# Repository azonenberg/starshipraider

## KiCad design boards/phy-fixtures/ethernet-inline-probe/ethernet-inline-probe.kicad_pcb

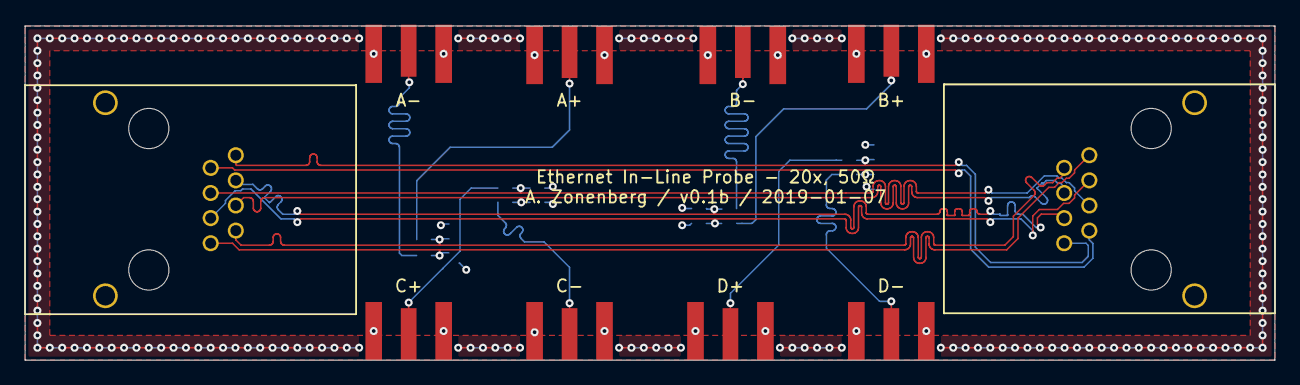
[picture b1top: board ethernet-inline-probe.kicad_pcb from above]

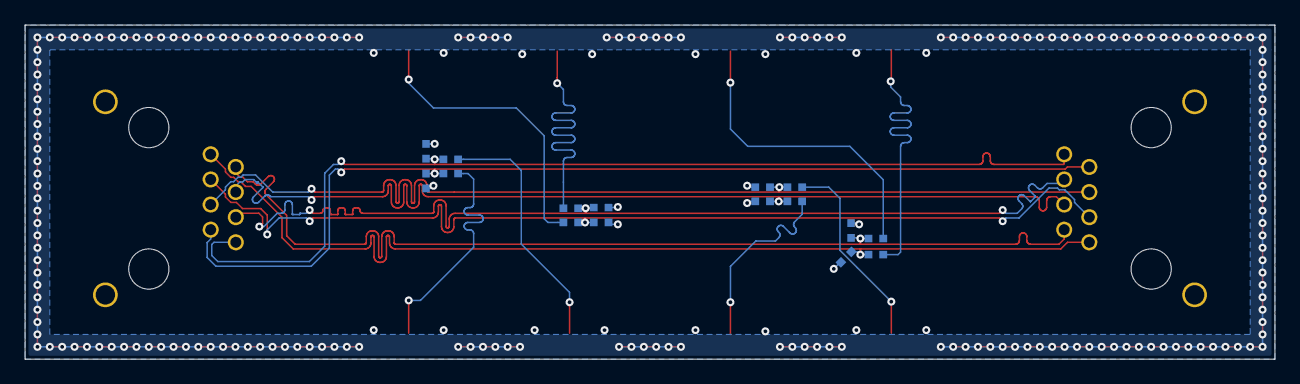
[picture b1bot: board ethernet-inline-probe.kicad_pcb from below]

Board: 4 copper layers, 101.0 x 27.0 mm, 26 parts (16 on the bottom side), 17 nets.

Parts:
J1, J6: STEWART_SS_60000_009; CONN_STEWART_SS60000_009
J2, J3, J4, J5, J7, J8, J9, J10: SMA-J-P-H-ST-EM1; CONN_SMA_EDGE_SAMTEC_SMA_J_P_H_ST_EM1
R1, R2, R3, R4, R5, R6, R7, R8: 953; EIA_0402_RES_NOSILK
R9, R10, R11, R12, R13, R14, R15, R16: 100K; EIA_0402_RES_NOSILK

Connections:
/CH1_N: J1.2, J6.2, R2.2, R10.2
/CH1_P: J1.1, J6.1, R1.2, R9.2
/CH2_N: J1.6, J6.6, R4.2, R12.2
/CH2_P: J1.3, J6.3, R3.2, R11.2
/CH3_N: J1.5, J6.5, R6.2, R14.2
/CH3_P: J1.4, J6.4, R5.2, R13.2
/CH4_N: J1.8, J6.8, R8.2, R16.2
/CH4_P: J1.7, J6.7, R7.2, R15.2
/GND: J1.9, J2.2, J3.2, J4.2, J5.2, J6.9, J7.2, J8.2, J9.2, J10.2, R9.1, R10.1, R11.1, R12.1, R13.1, R14.1, R15.1, R16.1
unnamed: J2.1, R1.1
unnamed: J3.1, R2.1
unnamed: J4.1, R3.1
unnamed: J5.1, R4.1
unnamed: J7.1, R5.1
unnamed: J8.1, R6.1
unnamed: J9.1, R7.1
unnamed: J10.1, R8.1

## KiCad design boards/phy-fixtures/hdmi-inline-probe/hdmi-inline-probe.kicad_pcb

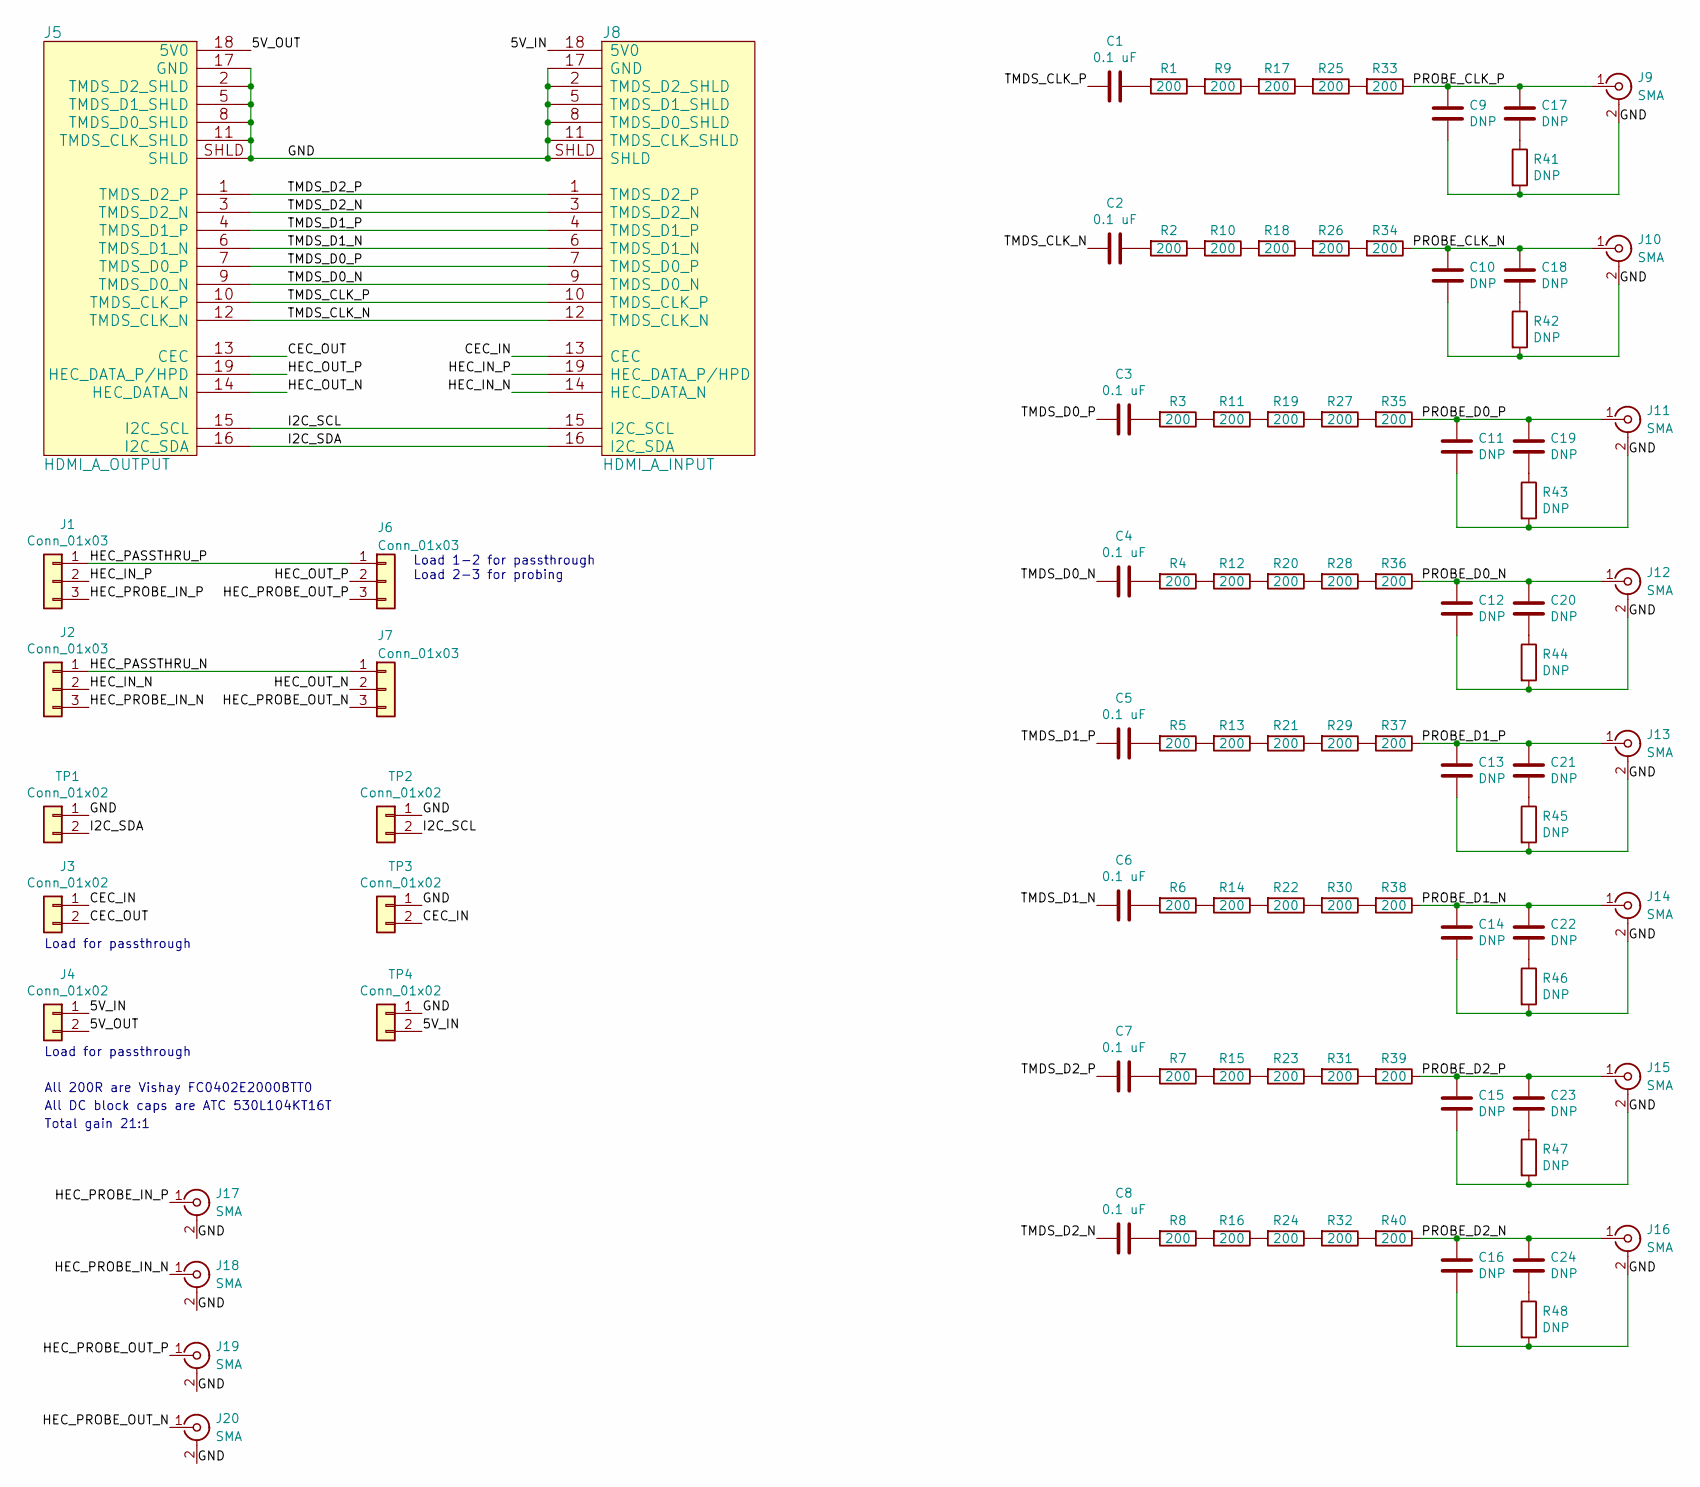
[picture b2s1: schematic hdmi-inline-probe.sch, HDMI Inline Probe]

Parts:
C1, C2, C3, C4, C5, C6, C7, C8: 0.1 uF; EIA_0402_CAP_NOSILK
C9, C10, C11, C12, C13, C14, C15, C16, C17, C18, C19, C20, C21, C22, C23, C24: DNP; EIA_0402_CAP_NOSILK
J1, J2, J6, J7: Conn_01x03; CONN_HEADER_2.54MM_1x3
J3, J4: Conn_01x02; CONN_HEADER_2.54MM_1x2
J5: HDMI_A_OUTPUT; CONN_HDMI_SAMTEC_HDMR_19_01_S_SM
J8: HDMI_A_INPUT; CONN_HDMI_SAMTEC_HDMR_19_01_S_SM
J9, J10, J11, J12, J13, J14, J15, J16, J17, J18, J19, J20: SMA; CONN_SMA_EDGE_SAMTEC_SMA_J_P_H_ST_EM1
R1, R2, R3, R4, R5, R6, R7, R8, R9, R10, R11, R12, R13, R14, R15, R16, R17, R18, R19, R20, R21, R22, R23, R24, R25, R26, R27, R28, R29, R30, R31, R32, R33, R34, R35, R36, R37, R38, R39, R40: 200; EIA_0402_RES_NOSILK
R41, R42, R43, R44, R45, R46, R47, R48: DNP; EIA_0402_RES_NOSILK
TP1, TP2, TP3, TP4: Conn_01x02; CONN_HEADER_2.54MM_1x2

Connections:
/5V_IN: J4.1, J8.18 (5V0), TP4.2
/5V_OUT: J4.2, J5.18 (5V0)
/CEC_IN: J3.1, J8.13 (CEC), TP3.2
/CEC_OUT: J3.2, J5.13 (CEC)
/GND: C9.2, C10.2, C11.2, C12.2, C13.2, C14.2, C15.2, C16.2, J5.2 (TMDS_D2_SHLD), J5.5 (TMDS_D1_SHLD), J5.8 (TMDS_D0_SHLD), J5.11 (TMDS_CLK_SHLD), J5.17 (GND), J5.SHLD, J8.2 (TMDS_D2_SHLD), J8.5 (TMDS_D1_SHLD), J8.8 (TMDS_D0_SHLD), J8.11 (TMDS_CLK_SHLD), J8.17 (GND), J8.SHLD, J9.2 (Ext), J10.2 (Ext), J11.2 (Ext), J12.2 (Ext), J13.2 (Ext), J14.2 (Ext), J15.2 (Ext), J16.2 (Ext), J17.2 (Ext), J18.2 (Ext), J19.2 (Ext), J20.2 (Ext), R41.2, R42.2, R43.2, R44.2, R45.2, R46.2, R47.2, R48.2, TP1.1, TP2.1, TP3.1, TP4.1
/HEC_IN_N: J2.2, J8.14 (HEC_DATA_N)
/HEC_IN_P: J1.2, J8.19 (HEC_DATA_P/HPD)
/HEC_OUT_N: J5.14 (HEC_DATA_N), J7.2
/HEC_OUT_P: J5.19 (HEC_DATA_P/HPD), J6.2
/HEC_PASSTHRU_N: J2.1, J7.1
/HEC_PASSTHRU_P: J1.1, J6.1
/HEC_PROBE_IN_N: J2.3, J18.1 (In)
/HEC_PROBE_IN_P: J1.3, J17.1 (In)
/HEC_PROBE_OUT_N: J7.3, J20.1 (In)
/HEC_PROBE_OUT_P: J6.3, J19.1 (In)
/I2C_SCL: J5.15 (I2C_SCL), J8.15 (I2C_SCL), TP2.2
/I2C_SDA: J5.16 (I2C_SDA), J8.16 (I2C_SDA), TP1.2
/PROBE_CLK_N: C10.1, C18.1, J10.1 (In), R34.1
/PROBE_CLK_P: C9.1, C17.1, J9.1 (In), R33.1
/PROBE_D0_N: C12.1, C20.1, J12.1 (In), R36.1
/PROBE_D0_P: C11.1, C19.1, J11.1 (In), R35.1
/PROBE_D1_N: C14.1, C22.1, J14.1 (In), R38.1
/PROBE_D1_P: C13.1, C21.1, J13.1 (In), R37.1
/PROBE_D2_N: C16.1, C24.1, J16.1 (In), R40.1
/PROBE_D2_P: C15.1, C23.1, J15.1 (In), R39.1
/TMDS_CLK_N: C2.2, J5.12 (TMDS_CLK_N), J8.12 (TMDS_CLK_N)
/TMDS_CLK_P: C1.2, J5.10 (TMDS_CLK_P), J8.10 (TMDS_CLK_P)
/TMDS_D0_N: C4.2, J5.9 (TMDS_D0_N), J8.9 (TMDS_D0_N)
/TMDS_D0_P: C3.2, J5.7 (TMDS_D0_P), J8.7 (TMDS_D0_P)
/TMDS_D1_N: C6.2, J5.6 (TMDS_D1_N), J8.6 (TMDS_D1_N)
/TMDS_D1_P: C5.2, J5.4 (TMDS_D1_P), J8.4 (TMDS_D1_P)
/TMDS_D2_N: C8.2, J5.3 (TMDS_D2_N), J8.3 (TMDS_D2_N)
/TMDS_D2_P: C7.2, J5.1 (TMDS_D2_P), J8.1 (TMDS_D2_P)
unnamed: C1.1, R1.2
unnamed: C2.1, R2.2
unnamed: C3.1, R3.2
unnamed: C4.1, R4.2
unnamed: C5.1, R5.2
unnamed: C6.1, R6.2
unnamed: C7.1, R7.2
unnamed: C8.1, R8.2
unnamed: C17.2, R41.1
unnamed: C18.2, R42.1
unnamed: C19.2, R43.1
unnamed: C20.2, R44.1
unnamed: C21.2, R45.1
unnamed: C22.2, R46.1
unnamed: C23.2, R47.1
unnamed: C24.2, R48.1
unnamed: R1.1, R9.2
unnamed: R10.1, R18.2
unnamed: R2.1, R10.2
unnamed: R11.1, R19.2
unnamed: R3.1, R11.2
unnamed: R12.1, R20.2
unnamed: R4.1, R12.2
unnamed: R13.1, R21.2
unnamed: R5.1, R13.2
unnamed: R14.1, R22.2
unnamed: R6.1, R14.2
unnamed: R15.1, R23.2
unnamed: R7.1, R15.2
unnamed: R16.1, R24.2
unnamed: R8.1, R16.2
unnamed: R17.1, R25.2
unnamed: R9.1, R17.2
unnamed: R18.1, R26.2
unnamed: R19.1, R27.2
unnamed: R20.1, R28.2
unnamed: R21.1, R29.2
unnamed: R22.1, R30.2
unnamed: R23.1, R31.2
unnamed: R24.1, R32.2
unnamed: R25.1, R33.2
unnamed: R26.1, R34.2
unnamed: R27.1, R35.2
unnamed: R28.1, R36.2
unnamed: R29.1, R37.2
unnamed: R30.1, R38.2
unnamed: R31.1, R39.2
unnamed: R32.1, R40.2

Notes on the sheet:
Load 1-2 for passthrough Load 2-3 for probing
All 200R are Vishay FC0402E2000BTT0
All DC block caps are ATC 530L104KT16T
Total gain 21:1
Load for passthrough

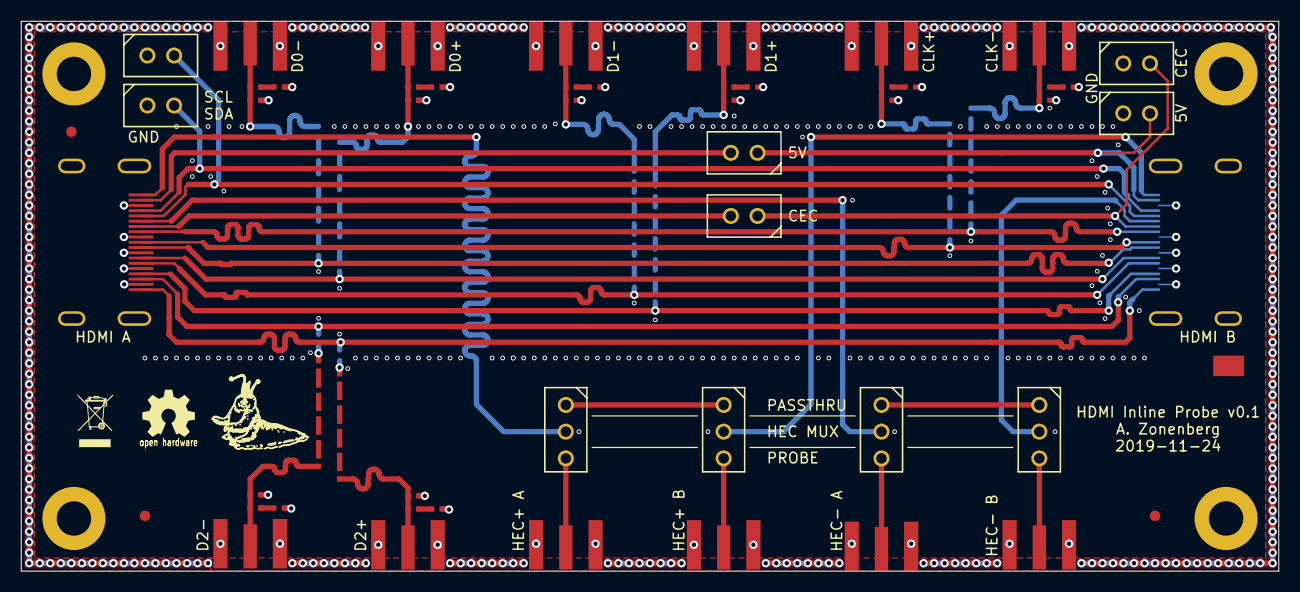
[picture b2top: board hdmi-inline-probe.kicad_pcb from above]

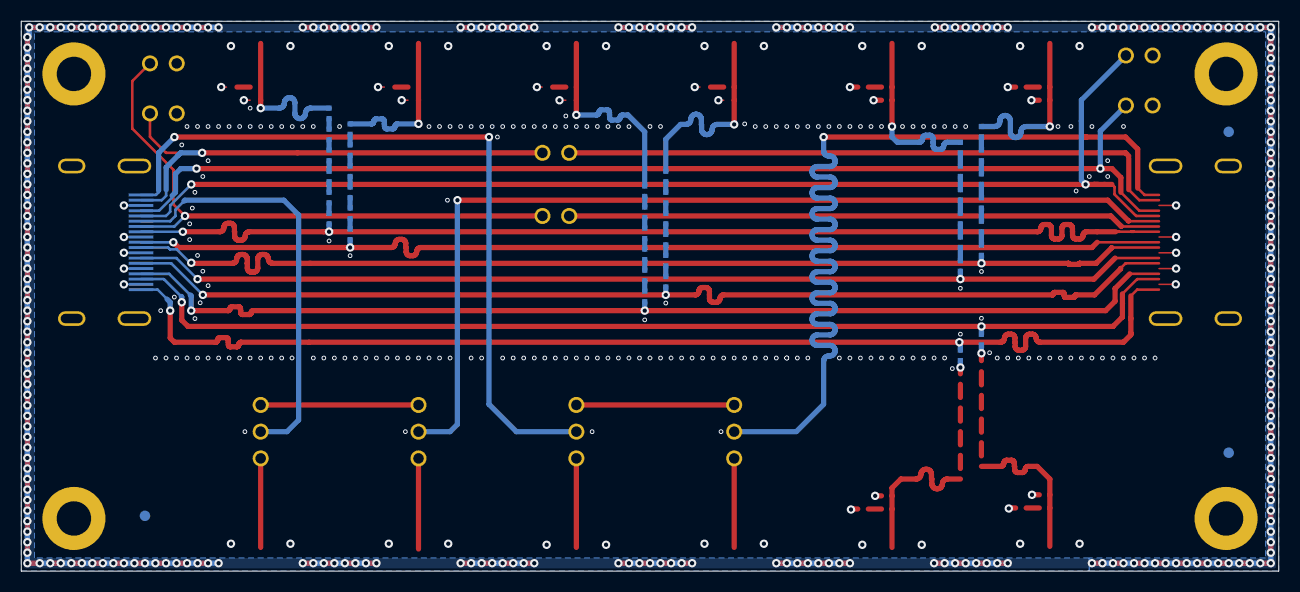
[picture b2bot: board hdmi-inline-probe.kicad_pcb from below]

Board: 4 copper layers, 119.5 x 52.2 mm, 102 parts (42 on the bottom side), 81 nets.

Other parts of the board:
FIDUCIAL_1MM, FIDUCIAL_1MM#2, FIDUCIAL_1MM#3, FIDUCIAL_1MM#4, FIDUCIAL_1MM#5, FIDUCIAL_1MM#6: VAL**; FIDUCIAL_1MM

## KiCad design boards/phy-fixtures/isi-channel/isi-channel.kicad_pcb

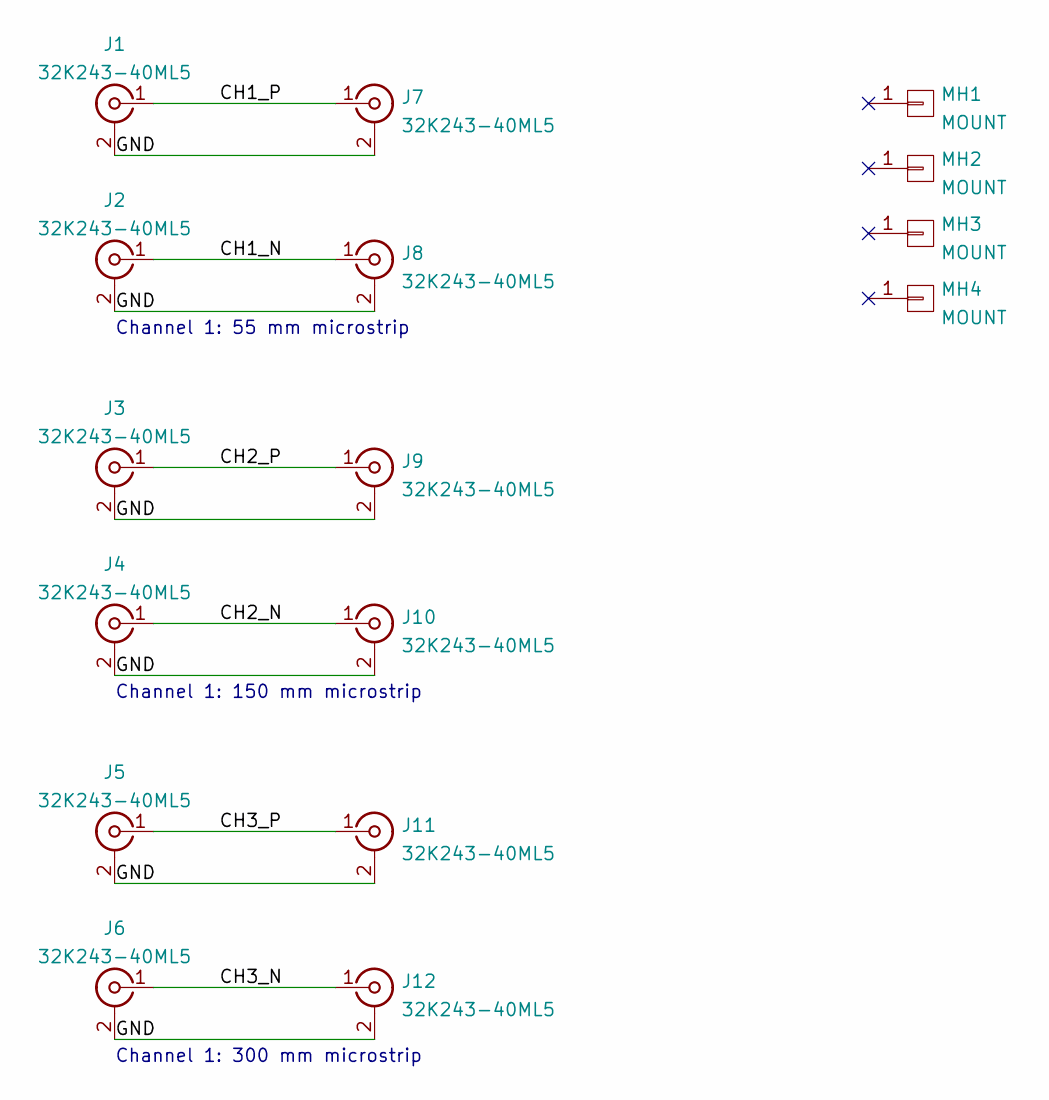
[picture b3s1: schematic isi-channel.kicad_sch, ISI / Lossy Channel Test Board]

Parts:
J1, J2, J3, J4, J5, J6, J7, J8, J9, J10, J11, J12: 32K243-40ML5; CONN_SMA_EDGE_ROSENBERGER_32K243_40ML5
MH1, MH2, MH3, MH4: MOUNT; MECHANICAL_CLEARANCEHOLE_4_40

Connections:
/CH1_N: J2.1 (In), J8.1 (In)
/CH1_P: J1.1 (In), J7.1 (In)
/CH2_N: J4.1 (In), J10.1 (In)
/CH2_P: J3.1 (In), J9.1 (In)
/CH3_N: J6.1 (In), J12.1 (In)
/CH3_P: J5.1 (In), J11.1 (In)
/GND: J1.2 (Ext), J2.2 (Ext), J3.2 (Ext), J4.2 (Ext), J5.2 (Ext), J6.2 (Ext), J7.2 (Ext), J8.2 (Ext), J9.2 (Ext), J10.2 (Ext), J11.2 (Ext), J12.2 (Ext)

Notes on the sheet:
Channel 1: 55 mm microstrip
Channel 1: 150 mm microstrip
Channel 1: 300 mm microstrip

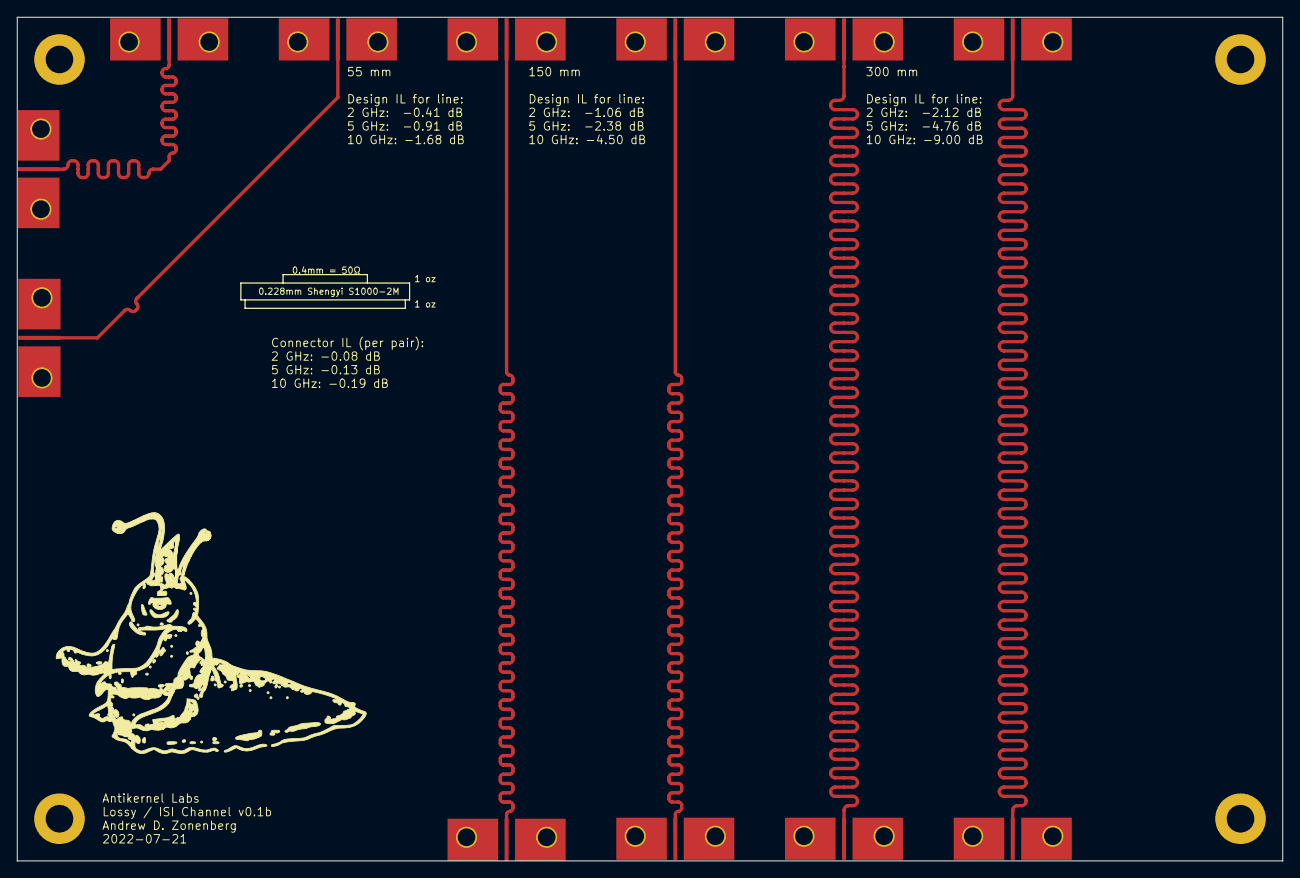
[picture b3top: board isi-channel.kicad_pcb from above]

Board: 4 copper layers, 150.0 x 100.0 mm, 16 parts (0 on the bottom side), 7 nets.

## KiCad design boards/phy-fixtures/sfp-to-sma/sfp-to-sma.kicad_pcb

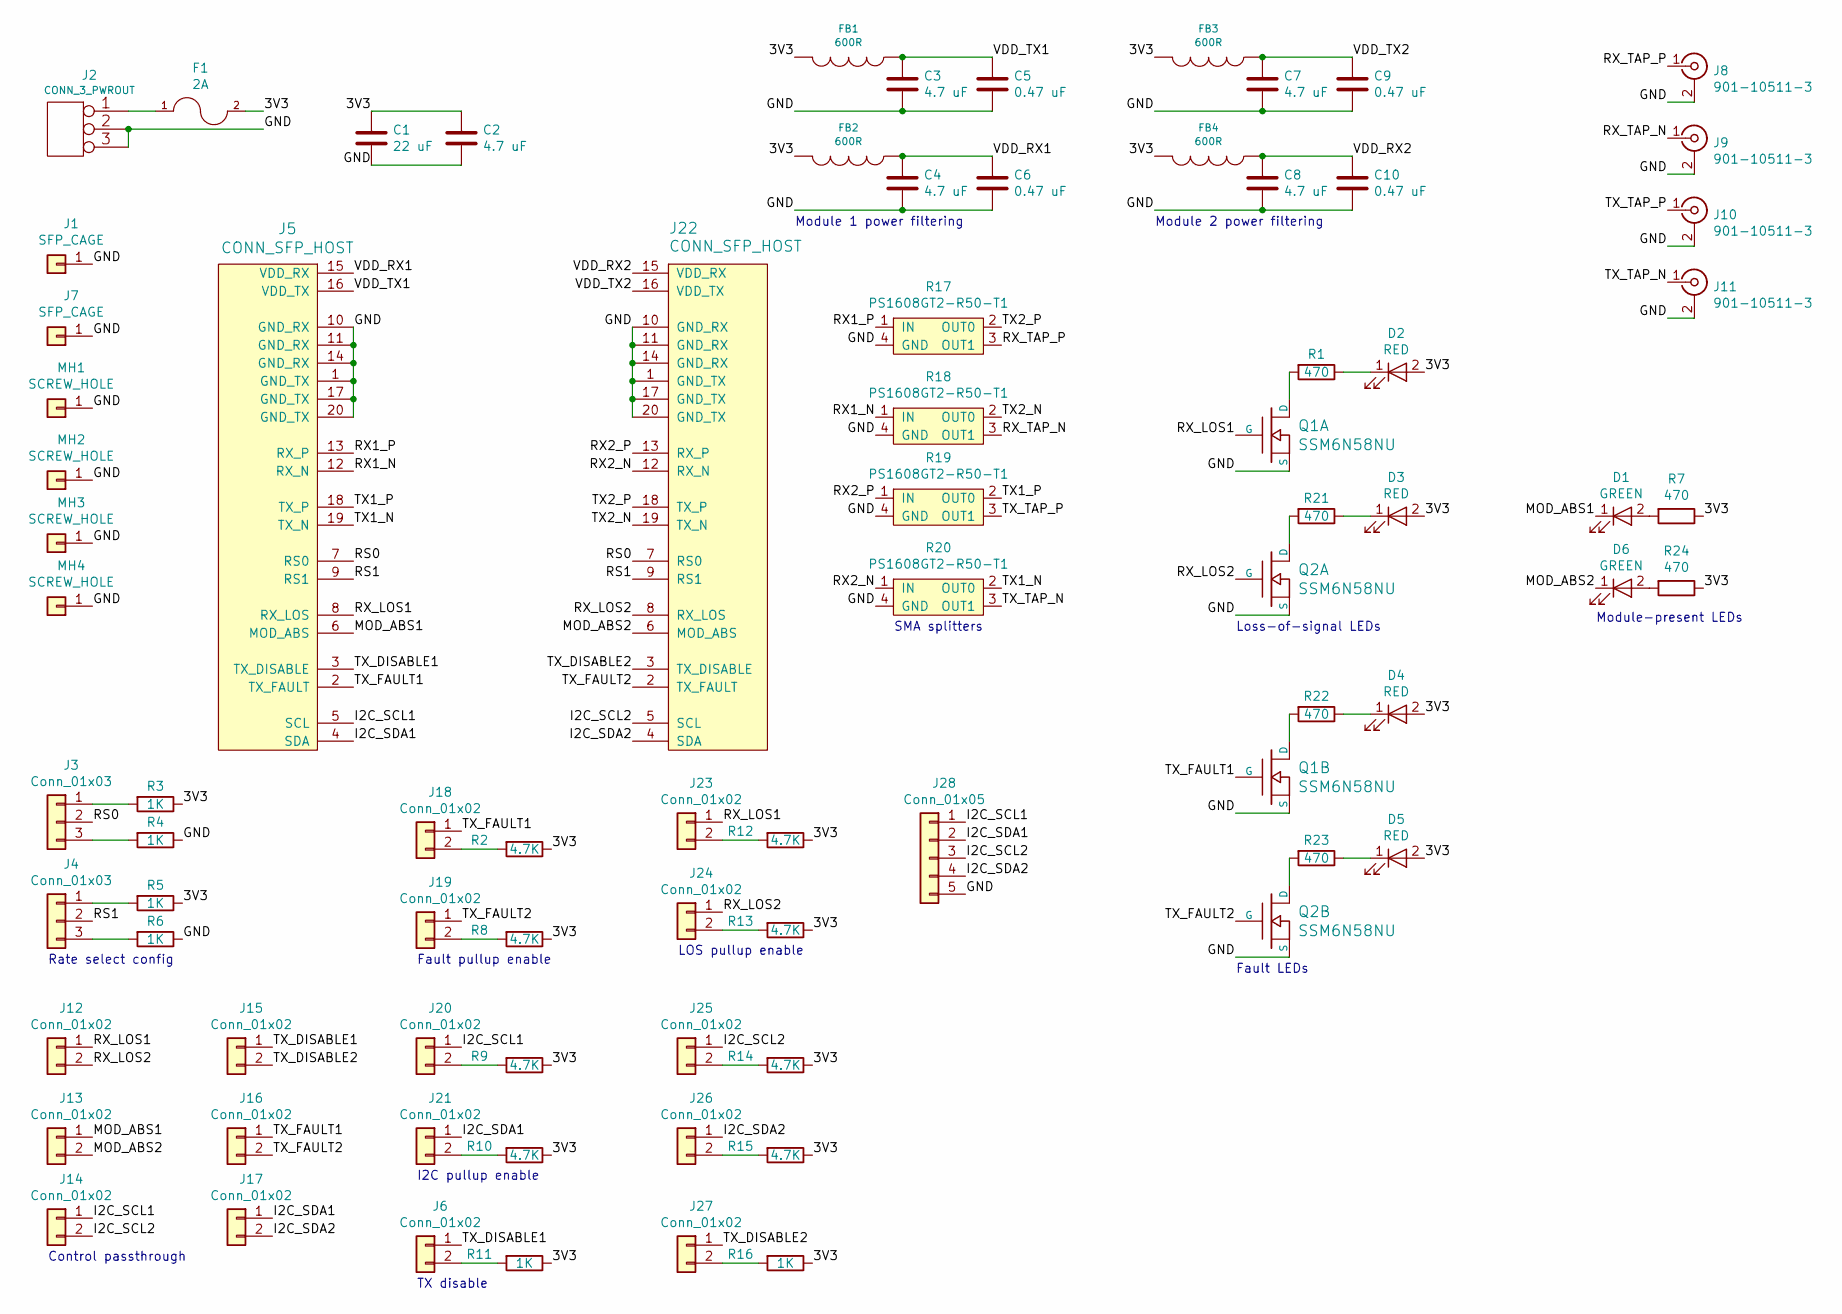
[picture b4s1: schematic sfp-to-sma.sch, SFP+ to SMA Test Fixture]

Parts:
C1: 22 uF; EIA_0805_CAP_NOSILK
C2, C3, C4, C7, C8: 4.7 uF; EIA_0603_CAP_NOSILK
C5, C6, C9, C10: 0.47 uF; EIA_0402_CAP_NOSILK
D1, D6: GREEN; EIA_0603_LED
D2, D3, D4, D5: RED; EIA_0603_LED
F1: 2A; EIA_0603_RES_NOSILK
FB1, FB2, FB3, FB4: 600R; EIA_0603_INDUCTOR_NOSILK
J1, J7: SFP_CAGE; CONN_SFP_CAGE_TE_2007194-1
J2: CONN_3_PWROUT; CONN_CUI_PJ-058BH_HIPWR_BARREL_NOSLOT
J3, J4: Conn_01x03; CONN_HEADER_2.54MM_1x3
J5, J22: CONN_SFP_HOST; CONN_SFP+_AMPHENOL_UE76_A10_2000T
J6, J12, J13, J14, J15, J16, J17, J18, J19, J20, J21, J23, J24, J25, J26, J27: Conn_01x02; CONN_HEADER_2.54MM_1x2
J8, J9, J10, J11: 901-10511-3; CONN_SMA_EDGE_AMPHENOL_901_10511_3
J28: Conn_01x05; CONN_HEADER_2.54MM_1x5
MH1, MH2, MH3, MH4: SCREW_HOLE; MECHANICAL_CLEARANCEHOLE_4_40
Q1, Q2: SSM6N58NU; DFN_6_0.65MM_2x2MM_GDS
R1, R7, R21, R22, R23, R24: 470; EIA_0402_RES_NOSILK
R2, R8, R9, R10, R12, R13, R14, R15: 4.7K; EIA_0402_RES_NOSILK
R3, R4, R5, R6, R11, R16: 1K; EIA_0402_RES_NOSILK
R17, R18, R19, R20: PS1608GT2-R50-T1; SPLITTER_SUSUMU_PS1608G

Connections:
/3V3: C1.1, C2.1, D2.2 (A), D3.2 (A), D4.2 (A), D5.2 (A), F1.2, FB1.2, FB2.2, FB3.2, FB4.2, R2.1, R3.1, R5.1, R7.1, R8.1, R9.1, R10.1, R11.1, R12.1, R13.1, R14.1, R15.1, R16.1, R24.1
/GND: C1.2, C2.2, C3.2, C4.2, C5.2, C6.2, C7.2, C8.2, C9.2, C10.2, J1.1, J2.2 (PM), J2.3, J5.1 (GND_TX), J5.10 (GND_RX), J5.11 (GND_RX), J5.14 (GND_RX), J5.17 (GND_TX), J5.20 (GND_TX), J7.1, J8.2 (Ext), J9.2 (Ext), J10.2 (Ext), J11.2 (Ext), J22.1 (GND_TX), J22.10 (GND_RX), J22.11 (GND_RX), J22.14 (GND_RX), J22.17 (GND_TX), J22.20 (GND_TX), J28.5, MH1.1, MH2.1, MH3.1, MH4.1, Q1.S1 (S), Q1.S2 (S), Q2.S1 (S), Q2.S2 (S), R4.1, R6.1, R17.4 (GND), R18.4 (GND), R19.4 (GND), R20.4 (GND)
/I2C_SCL1: J5.5 (SCL), J14.1, J20.1, J28.1
/I2C_SCL2: J14.2, J22.5 (SCL), J25.1, J28.3
/I2C_SDA1: J5.4 (SDA), J17.1, J21.1, J28.2
/I2C_SDA2: J17.2, J22.4 (SDA), J26.1, J28.4
/MOD_ABS1: D1.1 (K), J5.6 (MOD_ABS), J13.1
/MOD_ABS2: D6.1 (K), J13.2, J22.6 (MOD_ABS)
/RS0: J3.2, J5.7 (RS0), J22.7 (RS0)
/RS1: J4.2, J5.9 (RS1), J22.9 (RS1)
/RX1_N: J5.12 (RX_N), R18.1 (IN)
/RX1_P: J5.13 (RX_P), R17.1 (IN)
/RX2_N: J22.12 (RX_N), R20.1 (IN)
/RX2_P: J22.13 (RX_P), R19.1 (IN)
/RX_LOS1: J5.8 (RX_LOS), J12.1, J23.1, Q1.G1 (G)
/RX_LOS2: J12.2, J22.8 (RX_LOS), J24.1, Q2.G1 (G)
/RX_TAP_N: J9.1 (In), R18.3 (OUT1)
/RX_TAP_P: J8.1 (In), R17.3 (OUT1)
/TX1_N: J5.19 (TX_N), R20.2 (OUT0)
/TX1_P: J5.18 (TX_P), R19.2 (OUT0)
/TX2_N: J22.19 (TX_N), R18.2 (OUT0)
/TX2_P: J22.18 (TX_P), R17.2 (OUT0)
/TX_DISABLE1: J5.3 (TX_DISABLE), J6.1, J15.1
/TX_DISABLE2: J15.2, J22.3 (TX_DISABLE), J27.1
/TX_FAULT1: J5.2 (TX_FAULT), J16.1, J18.1, Q1.G2 (G)
/TX_FAULT2: J16.2, J19.1, J22.2 (TX_FAULT), Q2.G2 (G)
/TX_TAP_N: J11.1 (In), R20.3 (OUT1)
/TX_TAP_P: J10.1 (In), R19.3 (OUT1)
/VDD_RX1: C4.1, C6.1, FB2.1, J5.15 (VDD_RX)
/VDD_RX2: C8.1, C10.1, FB4.1, J22.15 (VDD_RX)
/VDD_TX1: C3.1, C5.1, FB1.1, J5.16 (VDD_TX)
/VDD_TX2: C7.1, C9.1, FB3.1, J22.16 (VDD_TX)
unnamed: D1.2 (A), R7.2
unnamed: D2.1 (K), R1.1
unnamed: D3.1 (K), R21.1
unnamed: D4.1 (K), R22.1
unnamed: D5.1 (K), R23.1
unnamed: D6.2 (A), R24.2
unnamed: F1.1, J2.1
unnamed: J3.1, R3.2
unnamed: J3.3, R4.2
unnamed: J4.1, R5.2
unnamed: J4.3, R6.2
unnamed: J6.2, R11.2
unnamed: J18.2, R2.2
unnamed: J19.2, R8.2
unnamed: J20.2, R9.2
unnamed: J21.2, R10.2
unnamed: J23.2, R12.2
unnamed: J24.2, R13.2
unnamed: J25.2, R14.2
unnamed: J26.2, R15.2
unnamed: J27.2, R16.2
unnamed: Q1.D1 (D), R1.2
unnamed: Q1.D2 (D), R22.2
unnamed: Q2.D1 (D), R21.2
unnamed: Q2.D2 (D), R23.2

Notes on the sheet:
Rate select config
Control passthrough
I2C pullup enable
TX disable
Module-present LEDs
LOS pullup enable
Module 1 power filtering
Module 2 power filtering
SMA splitters
Loss-of-signal LEDs
Fault pullup enable
Fault LEDs

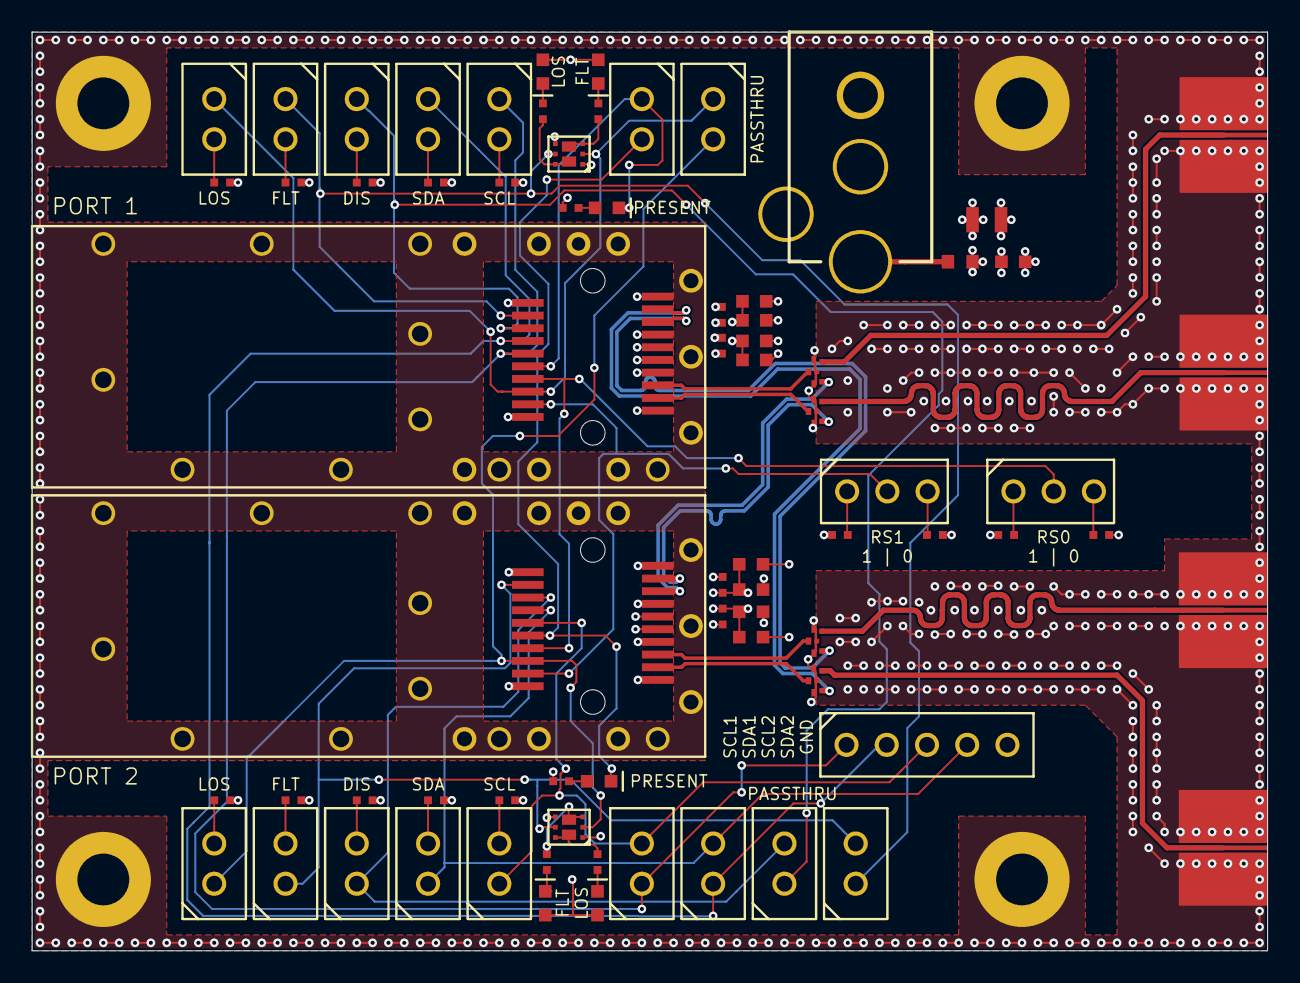
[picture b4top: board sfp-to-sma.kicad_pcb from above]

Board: 4 copper layers, 78.0 x 58.0 mm, 79 parts (0 on the bottom side), 57 nets.

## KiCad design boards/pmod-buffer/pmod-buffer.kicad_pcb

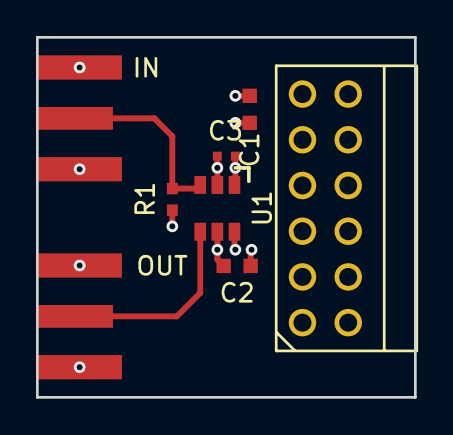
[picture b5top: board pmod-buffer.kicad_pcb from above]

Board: 4 copper layers, 21.0 x 20.0 mm, 8 parts (0 on the bottom side), 4 nets.

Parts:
C1, C2: 4.7 uF; EIA_0603_CAP_NOSILK
C3: 0.47 uF; EIA_0402_CAP_NOSILK
J1: PMOD_DEVICE_DIFF; CONN_HEADER_2.54MM_2x6_RA_PMOD_MODULE
P1, P2: SMA; CONN_SMA_EDGE_SAMTEC_SMA_J_P_H_ST_EM1
R1: 49.9; EIA_0402_RES_NOSILK
U1: 74AVC1T45; SOT23_6

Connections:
/3V3: C1.1, C2.1, C3.1, J1.6, J1.12, U1.1, U1.5, U1.6
/GND: C1.2, C2.2, C3.2, J1.5, J1.11, P1.2, P2.2, R1.2, U1.2
/VIN: P1.1, R1.1, U1.3
/VOUT: P2.1, U1.4

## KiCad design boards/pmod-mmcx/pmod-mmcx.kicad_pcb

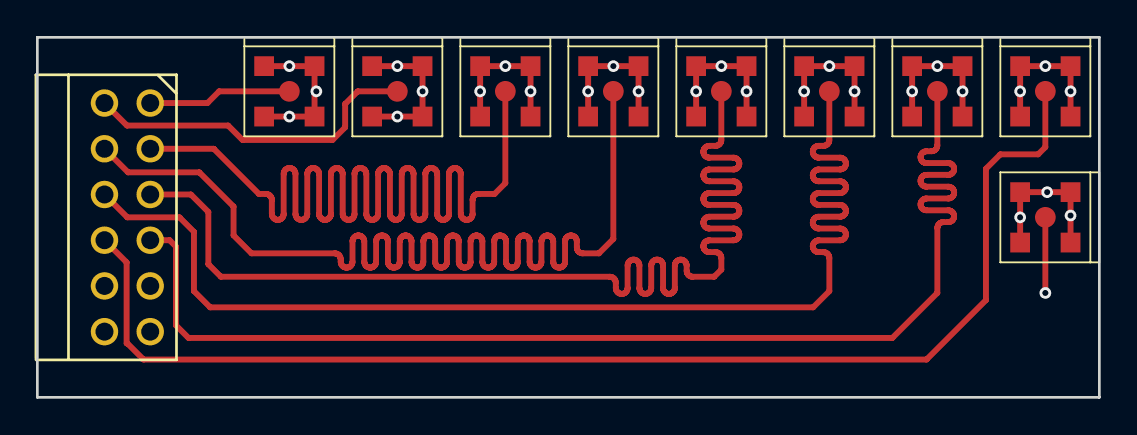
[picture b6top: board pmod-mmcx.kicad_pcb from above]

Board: 4 copper layers, 59.0 x 20.0 mm, 10 parts (0 on the bottom side), 10 nets.

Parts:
J1: PMOD_DEVICE_DIFF; CONN_HEADER_2.54MM_2x6_RA_PMOD_MODULE
P1, P2, P3, P4, P5, P6, P7, P8, P9: MMCX; CONN_MMCX_LINX_CONNMMCX002SMD

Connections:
/3V3: J1.6, J1.12, P9.1
/DQ0: J1.1, P1.1
/DQ1: J1.2, P2.1
/DQ2: J1.3, P3.1
/DQ3: J1.4, P4.1
/DQ4: J1.7, P5.1
/DQ5: J1.8, P6.1
/DQ6: J1.9, P7.1
/DQ7: J1.10, P8.1
/GND: J1.5, J1.11, P1.2, P2.2, P3.2, P4.2, P5.2, P6.2, P7.2, P8.2, P9.2

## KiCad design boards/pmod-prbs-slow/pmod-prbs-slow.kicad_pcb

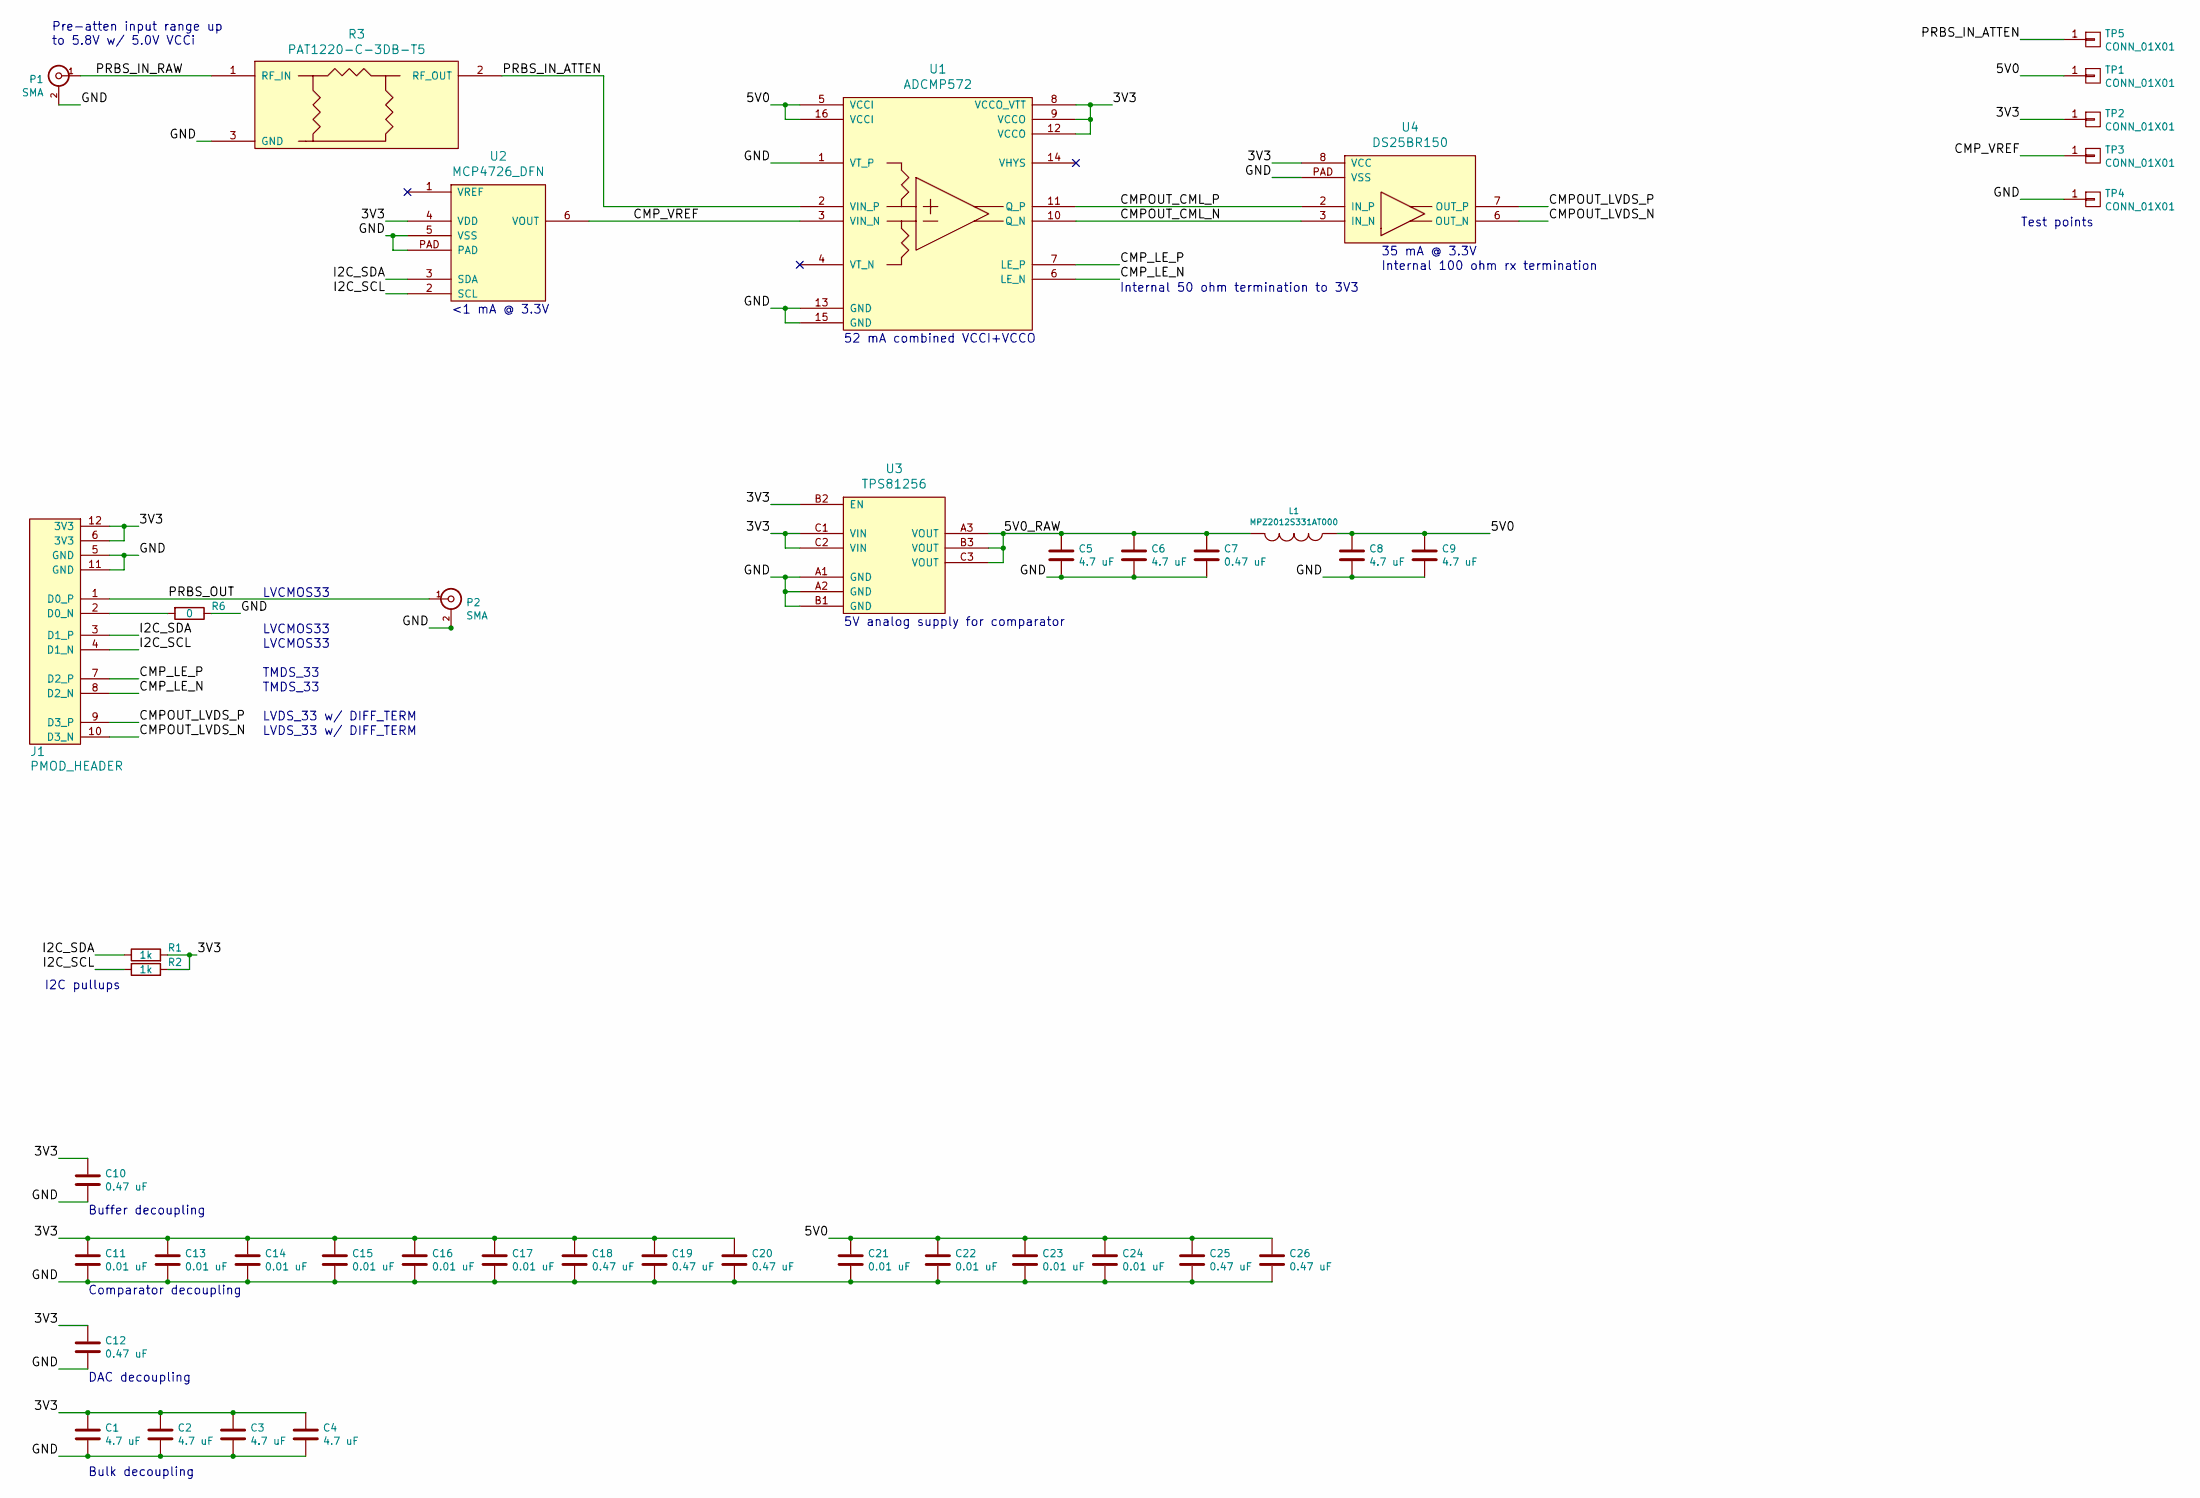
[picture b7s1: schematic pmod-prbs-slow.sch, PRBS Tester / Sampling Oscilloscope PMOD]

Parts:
C1, C2, C3, C4, C5, C6, C8, C9: 4.7 uF; EIA_0603_CAP_NOSILK
C7, C10, C12, C18, C19, C20, C25, C26: 0.47 uF; EIA_0402_CAP_NOSILK
C11, C13, C14, C15, C16, C17, C21, C22, C23, C24: 0.01 uF; EIA_0402_CAP_NOSILK
J1: PMOD_HEADER; CONN_HEADER_2.54MM_2x6_RA_PMOD_MODULE
L1: MPZ2012S331AT000; EIA_0805_INDUCTOR_NOSILK
P1, P2: SMA; CONN_SMA_EDGE_SAMTEC_SMA_J_P_H_ST_EM1
R1, R2: 1k; EIA_0402_RES_NOSILK
R3: PAT1220-C-3DB-T5; EIA_0805_PI_ATTENUATOR
R6: 0; EIA_0402_RES_NOSILK
TP1, TP2, TP3, TP5: CONN_01X01; TESTPOINT_SMT_0.5MM
TP4: CONN_01X01; TESTPOINT_SMT_KEYSTONE_5016
U1: ADCMP572; QFN_16_0.5MM_3x3MM
U2: MCP4726_DFN; DFN_6_0.65MM_2x2MM
U3: TPS81256; BGA_9_3x3_1MM_TI_SIP
U4: DS25BR150; DFN_8_0.5MM_3x3MM

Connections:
/3V3: C1.1, C2.1, C3.1, C4.1, C10.1, C11.1, C12.1, C13.1, C14.1, C15.1, C16.1, C17.1, C18.1, C19.1, C20.1, J1.6 (3V3), J1.12 (3V3), R1.2, R2.2, TP2.1, U1.8 (VCCO_VTT), U1.9 (VCCO), U1.12 (VCCO), U2.4 (VDD), U3.B2 (EN), U3.C1 (VIN), U3.C2 (VIN), U4.8 (VCC)
/5V0: C8.1, C9.1, C21.1, C22.1, C23.1, C24.1, C25.1, C26.1, L1.1, TP1.1, U1.5 (VCCI), U1.16 (VCCI)
/5V0_RAW: C5.1, C6.1, C7.1, L1.2, U3.A3 (VOUT), U3.B3 (VOUT), U3.C3 (VOUT)
/CMPOUT_CML_N: U1.10 (Q_N), U4.3 (IN_N)
/CMPOUT_CML_P: U1.11 (Q_P), U4.2 (IN_P)
/CMPOUT_LVDS_N: J1.10 (D3_N), U4.6 (OUT_N)
/CMPOUT_LVDS_P: J1.9 (D3_P), U4.7 (OUT_P)
/CMP_LE_N: J1.8 (D2_N), U1.6 (LE_N)
/CMP_LE_P: J1.7 (D2_P), U1.7 (LE_P)
/CMP_VREF: TP3.1, U1.3 (VIN_N), U2.6 (VOUT)
/GND: C1.2, C2.2, C3.2, C4.2, C5.2, C6.2, C7.2, C8.2, C9.2, C10.2, C11.2, C12.2, C13.2, C14.2, C15.2, C16.2, C17.2, C18.2, C19.2, C20.2, C21.2, C22.2, C23.2, C24.2, C25.2, C26.2, J1.5 (GND), J1.11 (GND), P1.2 (Ext), P2.2 (Ext), R3.3 (GND), R6.1, TP4.1, U1.1 (VT_P), U1.13 (GND), U1.15 (GND), U2.5 (VSS), U2.PAD, U3.A1 (GND), U3.A2 (GND), U3.B1 (GND), U4.PAD (VSS)
/I2C_SCL: J1.4 (D1_N), R2.1, U2.2 (SCL)
/I2C_SDA: J1.3 (D1_P), R1.1, U2.3 (SDA)
/PRBS_IN_ATTEN: R3.2 (RF_OUT), TP5.1, U1.2 (VIN_P)
/PRBS_IN_RAW: P1.1 (In), R3.1 (RF_IN)
/PRBS_OUT: J1.1 (D0_P), P2.1 (In)
unnamed: J1.2 (D0_N), R6.2

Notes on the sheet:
LVCMOS33
TMDS_33
LVDS_33 w/ DIFF_TERM
35 mA @ 3.3V
<1 mA @ 3.3V
52 mA combined VCCI+VCCO
Internal 100 ohm rx termination
Pre-atten input range up to 5.8V w/ 5.0V VCCi
Bulk decoupling
5V analog supply for comparator
DAC decoupling
Comparator decoupling
Buffer decoupling
Test points
I2C pullups
Internal 50 ohm termination to 3V3
